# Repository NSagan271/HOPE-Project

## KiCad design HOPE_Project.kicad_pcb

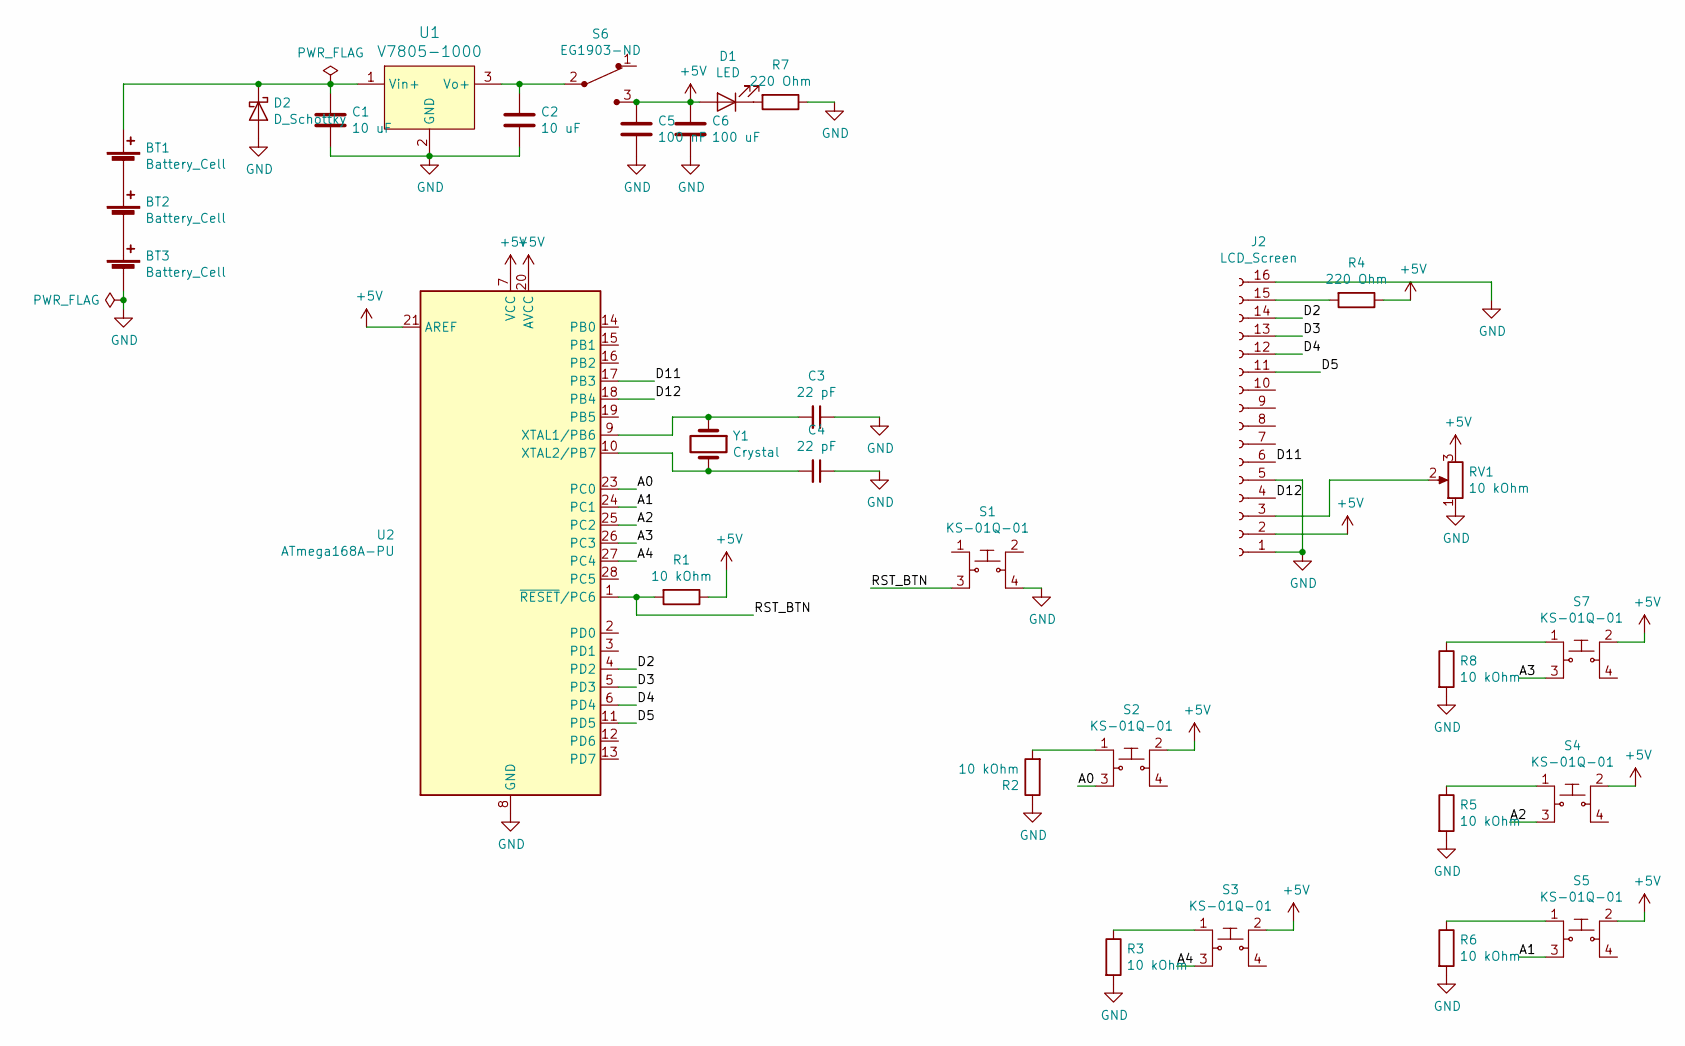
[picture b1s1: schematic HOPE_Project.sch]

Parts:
BT1, BT2, BT3: Battery_Cell; Battery_Holder_Coin_2032_BS-7
C1, C2: 10 uF; C_0805_2012Metric
C3, C4: 22 pF; C_0402_1005Metric
C5: 100 nF; C_0201_0603Metric
C6: 100 uF; C_1206_3216Metric
D1: LED; LED_0603_1608Metric
D2: D_Schottky; D_SOD-323
J2: LCD_Screen; LCD_20x4
R1, R2, R3, R5, R6, R8: 10 kOhm; R_0201_0603Metric
R4, R7: 220 Ohm; R_0201_0603Metric
RV1: 10 kOhm; Potentiometer_P120PK-Y25BR10K
S1, S2, S3, S4, S5, S7: KS-01Q-01; PushButton_Round_D12mm_THT_KS-01Q-01; MPN KS-01Q-01; Digi-Key_PN EG4791-ND
S6: EG1903-ND; Switch_Slide_11.6x4mm_EG1218
U1: V7805-1000; 3-SIP_Module_V7805-1000; MPN V7805-1000; Digi-Key_PN 102-1715-ND
U2: ATmega168A-PU; DIP-28_W7.62mm
Y1: Crystal; Crystal_HC49-U_Vertical

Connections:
+5V: C5.1, C6.1, D1.2 (A), J2.2, R1.1, R4.1, RV1.3, S2.2, S3.2, S4.2, S5.2, S6.3, S7.2, U2.7 (VCC), U2.20 (AVCC), U2.21 (AREF)
/A0: S2.3, U2.23 (PC0)
/A1: S5.3, U2.24 (PC1)
/A2: S4.3, U2.25 (PC2)
/A3: S7.3, U2.26 (PC3)
/A4: S3.3, U2.27 (PC4)
/D2: J2.14, U2.4 (PD2)
/D3: J2.13, U2.5 (PD3)
/D4: J2.12, U2.6 (PD4)
/D5: J2.11, U2.11 (PD5)
/D11: J2.6, U2.17 (PB3)
/D12: J2.4, U2.18 (PB4)
/RST_BTN: R1.2, S1.3, U2.1 (~RESET~/PC6)
GND: BT3.2 (-), C1.2, C2.2, C3.1, C4.1, C5.2, C6.2, D2.2 (A), J2.1, J2.5, J2.16, R2.1, R3.2, R5.2, R6.2, R7.1, R8.2, RV1.1, S1.4, U1.2 (GND), U2.8 (GND), U2.22 (GND)
unnamed: BT1.1 (+), C1.1, D2.1 (K), U1.1 (Vin+)
unnamed: BT1.2 (-), BT2.1 (+)
unnamed: BT2.2 (-), BT3.1 (+)
unnamed: C2.1, S6.2, U1.3 (Vo+)
unnamed: C3.2, U2.9 (XTAL1/PB6), Y1.1
unnamed: C4.2, U2.10 (XTAL2/PB7), Y1.2
unnamed: D1.1 (K), R7.2
unnamed: J2.3, RV1.2
unnamed: J2.15, R4.2
unnamed: R2.2, S2.1
unnamed: R3.1, S3.1
unnamed: R5.1, S4.1
unnamed: R6.1, S5.1
unnamed: R8.1, S7.1

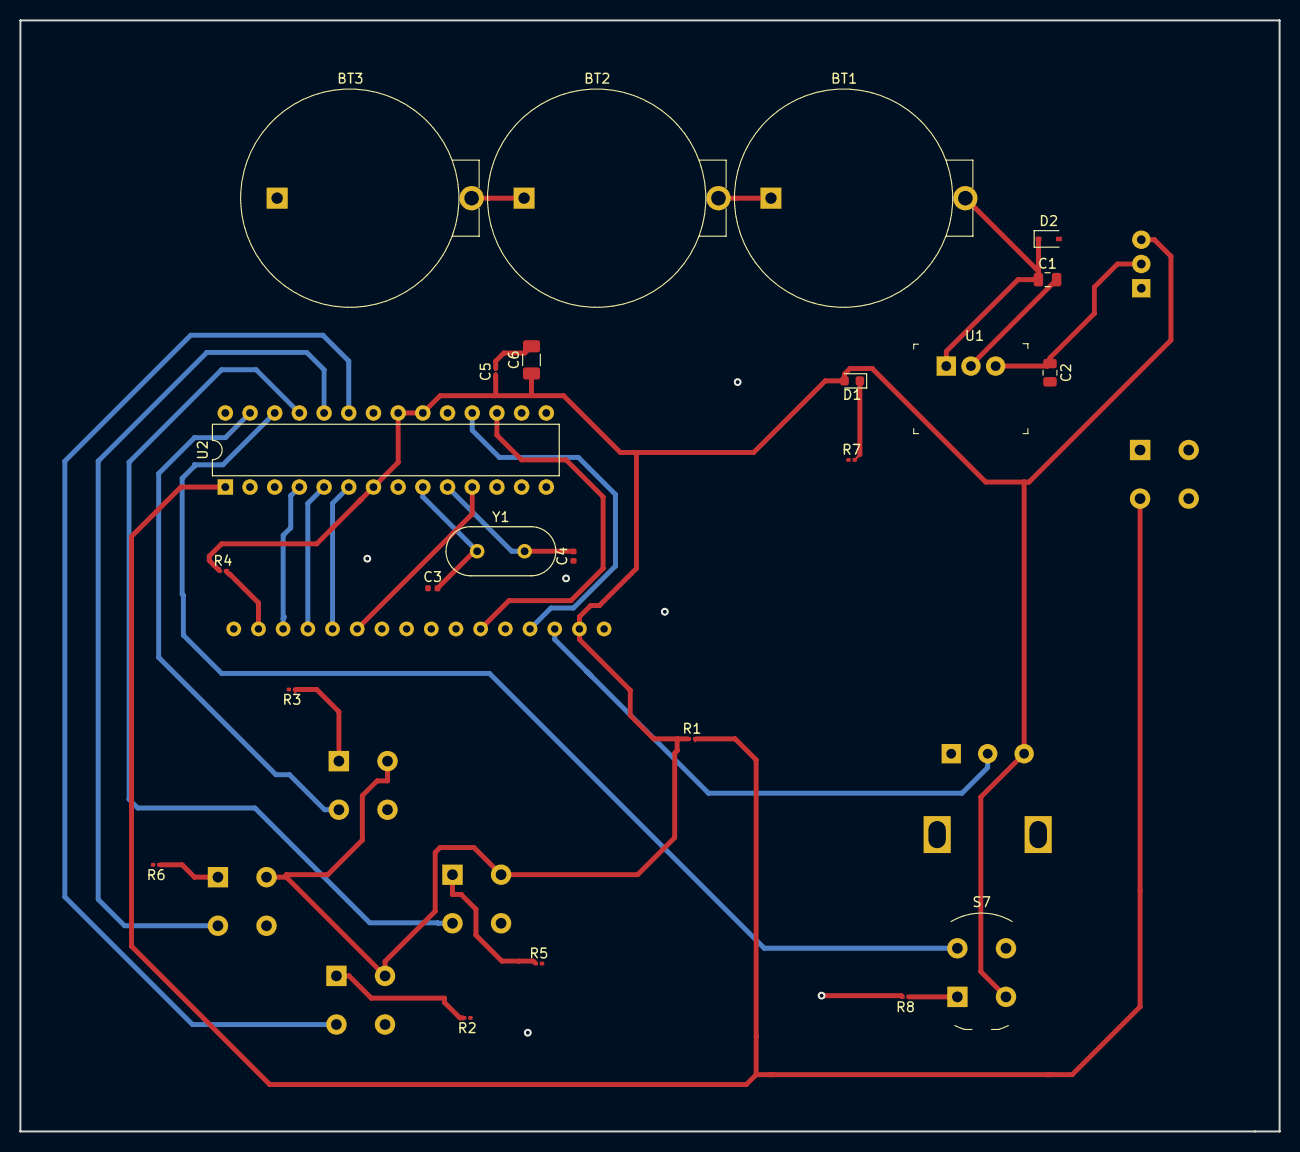
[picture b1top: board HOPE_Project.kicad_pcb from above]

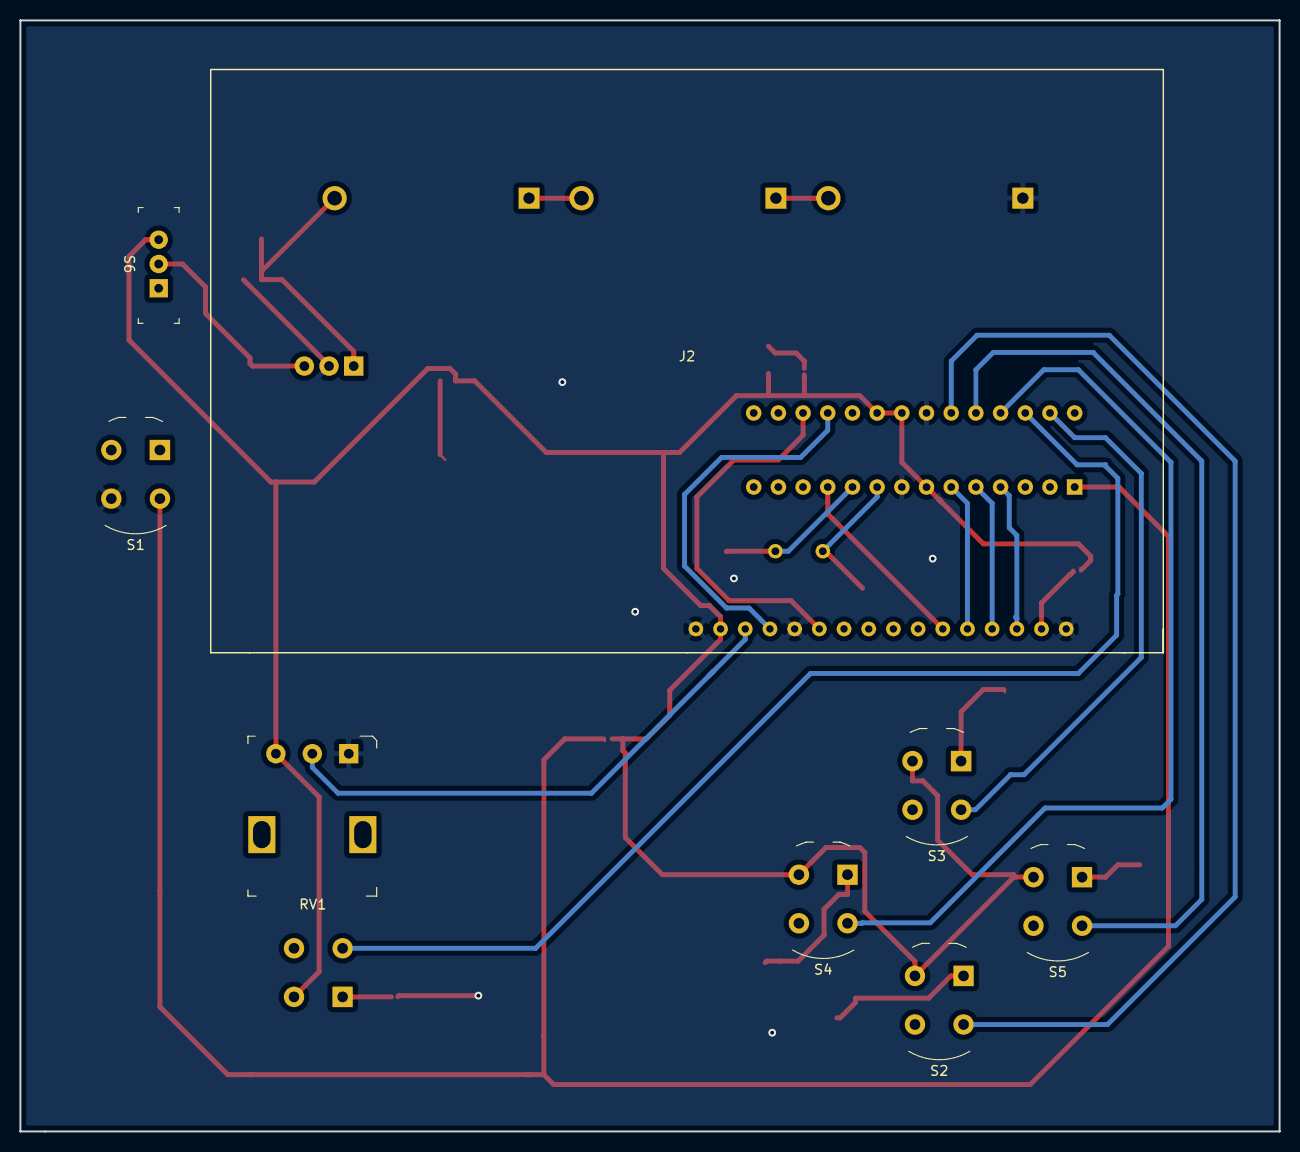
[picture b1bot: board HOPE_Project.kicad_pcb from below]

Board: 2 copper layers, 129.5 x 114.3 mm, 31 parts (8 on the bottom side), 28 nets.

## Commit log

2019-04-02 Add initial files
2019-04-02 Schematic bug fixes
2019-04-02 Change buttons on schematic
2019-04-02 Assign footprints
2019-04-02 Add footprint library
2019-04-04 Finish board
2019-04-04 First round of adjustments
